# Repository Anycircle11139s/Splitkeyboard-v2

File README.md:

# SPLIT-KEYBOARD-V2
The second attempt of creating the prefect split keyboard by @NotALarp
## WHAT IS IT?
This is my custom split keyboard made in KiCad, based on a LILY58 split keyboard design, it is sleek and is designed with ergonomics in mind. 

## Featured Hardware:
- Nice!Nano v2 microcontroller
- Lipo batteries
- Low profile choc switches
- 0.91" OLED displays
- EC11 Rotary Encoders

## WHY I MADE IT
My first split keyboard was pretty bad, it was based on a xiao nrf58240 microcontroller, had a terrible layout and overall wasn't that good. So I decided that with my previous knowledge that I would create a new, second split keyboard. 

## NOTES AND DESIGN CHOICES
This  time I decided to base the layout on a real split keyboard and some better microcontrollers. I decided on the nice!nano v2 and based the layout on a Lily58 split keyboard which I think looks really good. I designed a custom, 3d-printed case which was created to be compact, modern and sleek. 

## GALLERY

<br>

## BOM
<br>
https://docs.google.com/document/d/1G1sLWLXkf7hAwwnX9o8N8jDjILno_Bk2AuGZwasASP0/edit?usp=sharing

<br>

<br>

|Name                           |Purpose                                         |Quantity|Total Cost (USD)|Link                                                                                                                                                                                                                                                                                                                                                                                                                                                                                                                                                                                                                                                                                                                                                                                 |Distributor    |
|-------------------------------|------------------------------------------------|--------|----------------|-------------------------------------------------------------------------------------------------------------------------------------------------------------------------------------------------------------------------------------------------------------------------------------------------------------------------------------------------------------------------------------------------------------------------------------------------------------------------------------------------------------------------------------------------------------------------------------------------------------------------------------------------------------------------------------------------------------------------------------------------------------------------------------|---------------|
|M3 screws                      |To screw everything into place                  |1       |3.00            |https://www.aliexpress.com/item/1005008810897680.html?algo_exp_id=087b4537-d427-4093-becf-17723da02467-6&pdp_ext_f=%7B%22order%22%3A%2211108%22%2C%22spu_best_type%22%3A%22price%22%2C%22eval%22%3A%221%22%2C%22fromPage%22%3A%22search%22%7D&utparam-url=scene%3Asearch%7Cquery_from%3A%7Cx_object_id%3A1005008810897680%7C_p_origin_prod%3A                                                                                                                                                                                                                                                                                                                                                                                                                                        |Ali express    |
|Keycaps                        |to cover the switches                           |1       |25.00           |https://www.aliexpress.com/item/1005006734545486.html?algo_exp_id=1f377480-5edc-41ad-8720-dc378dbb9e71-0&pdp_ext_f=%7B%22order%22%3A%221046%22%2C%22spu_best_type%22%3A%22price%22%2C%22eval%22%3A%221%22%2C%22fromPage%22%3A%22search%22%7D&utparam-url=scene%3Asearch%7Cquery_from%3A%7Cx_object_id%3A1005006734545486%7C_p_origin_prod%3A                                                                                                                                                                                                                                                                                                                                                                                                                                         |Ali express    |
|Case shipping and printing     |The 3D printed case                             |1       |0.00            |                                                                                                                                                                                                                                                                                                                                                                                                                                                                                                                                                                                                                                                                                                                                                                                     |Printing Legion|
|PCB                            |To hold/wire everything together                |1       |26.00           |                                                                                                                                                                                                                                                                                                                                                                                                                                                                                                                                                                                                                                                                                                                                                                                     |JLCPCB         |
|Rubber Feat                    |to keep the keyboard in place while typing      |1       |3.00            |https://www.aliexpress.com/item/1005009513504427.html?spm=a2g0o.productlist.main.2.402aMWEOMWEOzm&algo_pvid=8754c733-74ec-46fa-a026-dd8beb2eaa2f&algo_exp_id=8754c733-74ec-46fa-a026-dd8beb2eaa2f-1&pdp_ext_f=%7B%22order%22%3A%22398%22%2C%22spu_best_type%22%3A%22price%22%2C%22eval%22%3A%221%22%2C%22fromPage%22%3A%22search%22%7D&pdp_npi=6%40dis%21AUD%215.20%212.76%21%21%2124.88%2113.19%21%402101d6fe17791895784877032e32a2%2112000049332590820%21sea%21AU%217402515296%21X%211%210%21n_tag%3A-29919%3Bd%3A1851364a%3Bm03_new_user%3A-29895&curPageLogUid=5WTu2EJR6cb9&utparam-url=scene%3Asearch%7Cquery_from%3A%7Cx_object_id%3A1005009513504427%7C_p_origin_prod%3A                                                                                                      |Ali express    |
|Lipo batteries                 |For making the thing have power while wireless  |2       |14.00           |https://www.aliexpress.com/item/32660019420.html?spm=a2g0o.productlist.main.18.2d67kd2Qkd2Q7m&utparam-url=scene%3Asearch%7Cquery_from%3Apc_back_same_best%7Cx_object_id%3A32660019420%7C_p_origin_prod%3A&algo_pvid=c45310cf-be00-4c95-97ef-f2f4c851b03d&algo_exp_id=c45310cf-be00-4c95-97ef-f2f4c851b03d&pdp_ext_f=%7B%22order%22%3A%22188%22%2C%22fromPage%22%3A%22search%22%7D&pdp_npi=6%40dis%21AUD%216.66%213.99%21%21%214.69%212.81%21%402101e2b417791893788974036e0b69%2112000032763467394%21sea%21AU%217402515296%21X%211%210%21n_tag%3A-29919%3Bd%3A1851364a%3Bm03_new_user%3A-29895                                                                                                                                                                                        |Ali express    |
|JST pin connector              |To connect Lipo batteries                       |1       |1.30            |https://www.aliexpress.com/item/1005004955655144.html?spm=a2g0o.productlist.main.2.2a7463el63el05&algo_pvid=54c753d9-8154-4c75-a2fe-a480a0edb504&algo_exp_id=54c753d9-8154-4c75-a2fe-a480a0edb504-1&pdp_ext_f=%7B%22order%22%3A%224230%22%2C%22spu_best_type%22%3A%22price%22%2C%22eval%22%3A%221%22%2C%22fromPage%22%3A%22search%22%7D&pdp_npi=6%40dis%21AUD%211.38%211.31%21%21%210.97%210.92%21%40210311a017791891742303314e881a%2112000031146362162%21sea%21AU%217402515296%21X%211%210%21n_tag%3A-29919%3Bd%3A1851364a%3Bm03_new_user%3A-29895%3BpisId%3A5000000207008434&curPageLogUid=SeM6XgBLqABt&utparam-url=scene%3Asearch%7Cquery_from%3A%7Cx_object_id%3A1005004955655144%7C_p_origin_prod%3A                                                                            |Ali express    |
|Nice!Nano 2 drop in replacement|Microcontroller                                 |2       |12.00           |https://www.aliexpress.com/item/1005012324856273.html?spm=a2g0o.productlist.main.1.5312262dHECxbc&algo_pvid=1d39c1dc-7c31-4a60-900f-a0e3a6a7fce5&algo_exp_id=1d39c1dc-7c31-4a60-900f-a0e3a6a7fce5-0&pdp_ext_f=%7B%22order%22%3A%22-1%22%2C%22eval%22%3A%221%22%2C%22fromPage%22%3A%22search%22%7D&pdp_npi=6%40dis%21AUD%2113.71%212.19%21%21%2165.60%2110.50%21%402101f70717791880964281024e130c%2112000058098750531%21sea%21AU%217402515296%21X%211%210%21n_tag%3A-29919%3Bd%3A1851364a%3Bm03_new_user%3A-29895&curPageLogUid=t0nqsjWoAD10&utparam-url=scene%3Asearch%7Cquery_from%3A%7Cx_object_id%3A1005012324856273%7C_p_origin_prod%3A                                                                                                                                          |Ali express    |
|Rotary encoder                 |The turning sensor for volume/brightness control|2       |4.00            |https://www.aliexpress.com/item/1005006693443387.html                                                                                                                                                                                                                                                                                                                                                                                                                                                                                                                                                                                                                                                                                                                                |Ali express    |
|2M resistors                   |Battery sensing                                 |1       |2.30            |https://www.aliexpress.com/item/1005006984056678.html?spm=a2g0o.productlist.main.2.6d2bUmeuUmeuJY&algo_pvid=8428e61f-ef37-4c8f-9459-c9210825d6e1&algo_exp_id=8428e61f-ef37-4c8f-9459-c9210825d6e1-1&pdp_ext_f=%7B%22order%22%3A%22130%22%2C%22eval%22%3A%221%22%2C%22fromPage%22%3A%22search%22%7D&pdp_npi=6%40dis%21AUD%213.46%212.25%21%21%2116.54%2110.75%21%402103119c17791879033745560e8319%2112000038943042455%21sea%21AU%217402515296%21X%211%210%21n_tag%3A-29919%3Bd%3A1851364a%3Bm03_new_user%3A-29895&curPageLogUid=W9kpVUtpsgGF&utparam-url=scene%3Asearch%7Cquery_from%3A%7Cx_object_id%3A1005006984056678%7C_p_origin_prod%3A                                                                                                                                          |Ali express    |
|806K resistors                 |Battery Sense                                   |1       |2.30            |https://www.aliexpress.com/item/1005005184230104.html?spm=a2g0o.productlist.main.1.9292CUbcCUbcad&algo_pvid=8aa98164-e46b-4dea-8cd4-d1d9d648231d&algo_exp_id=8aa98164-e46b-4dea-8cd4-d1d9d648231d-0&pdp_ext_f=%7B%22order%22%3A%2217%22%2C%22eval%22%3A%221%22%2C%22fromPage%22%3A%22search%22%7D&pdp_npi=6%40dis%21AUD%212.39%212.27%21%21%2111.44%2110.87%21%402101eee917791877058268014e6261%2112000032017018125%21sea%21AU%217402515296%21X%211%210%21n_tag%3A-29919%3Bd%3A1851364a%3Bm03_new_user%3A-29895%3BpisId%3A5000000207008434&curPageLogUid=3ZB85ZmHR85W&utparam-url=scene%3Asearch%7Cquery_from%3A%7Cx_object_id%3A1005005184230104%7C_p_origin_prod%3A                                                                                                                |Ali express    |
|OLEDs                          |Displays                                        |2       |5.00            |https://www.aliexpress.com/item/1005009252203585.html                                                                                                                                                                                                                                                                                                                                                                                                                                                                                                                                                                                                                                                                                                                                |Ali express    |
|Diodes                         |For individual keys to click                    |1       |2.70            |https://www.aliexpress.com/item/1005007536719404.html?spm=a2g0o.productlist.main.1.48163d00gFi5nW&algo_pvid=8ca45988-0ebf-453f-8dbb-d071bb0fd947&algo_exp_id=8ca45988-0ebf-453f-8dbb-d071bb0fd947-0&pdp_ext_f=%7B%22order%22%3A%2257%22%2C%22spu_best_type%22%3A%22price%22%2C%22eval%22%3A%221%22%2C%22fromPage%22%3A%22search%22%7D&pdp_npi=6%40dis%21AUD%212.77%212.63%21%21%2113.25%2112.58%21%402101e2b617791874734143805e957b%2112000041199095476%21sea%21AU%217402515296%21X%211%210%21n_tag%3A-29919%3Bd%3A1851364a%3Bm03_new_user%3A-29895%3BpisId%3A5000000207008434&curPageLogUid=7tkJWryZP639&utparam-url=scene%3Asearch%7Cquery_from%3A%7Cx_object_id%3A1005007536719404%7C_p_origin_prod%3A                                                                            |Ali express    |
|Low Profile Choc Switches      |Buttons for the keyboard                        |1       |20.00           |https://www.aliexpress.com/item/1005005883472162.html?spm=a2g0o.productlist.main.4.4228tPMqtPMq2f&aem_p4p_detail=20260519032953288267209607090002622299&algo_pvid=d4c045f7-fedf-4b6d-a05c-4b18a162da60&algo_exp_id=d4c045f7-fedf-4b6d-a05c-4b18a162da60-3&pdp_ext_f=%7B%22order%22%3A%22820%22%2C%22eval%22%3A%221%22%2C%22fromPage%22%3A%22search%22%7D&pdp_npi=6%40dis%21AUD%2125.03%2121.54%21%21%2117.62%2115.16%21%40210318a717791865937722085eaeff%2112000034695877976%21sea%21AU%217402515296%21X%211%210%21n_tag%3A-29919%3Bd%3A1851364a%3Bm03_new_user%3A-29895%3BpisId%3A5000000207013346&curPageLogUid=ecY0FsHMIH2l&utparam-url=scene%3Asearch%7Cquery_from%3A%7Cx_object_id%3A1005005883472162%7C_p_origin_prod%3A&search_p4p_id=20260519032953288267209607090002622299_1|Ali Express    |

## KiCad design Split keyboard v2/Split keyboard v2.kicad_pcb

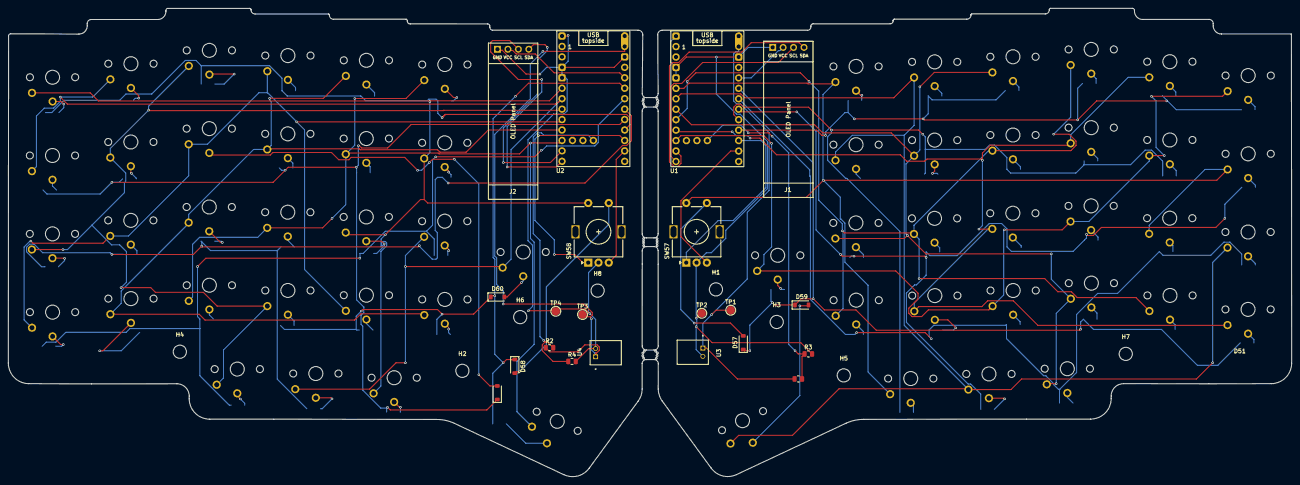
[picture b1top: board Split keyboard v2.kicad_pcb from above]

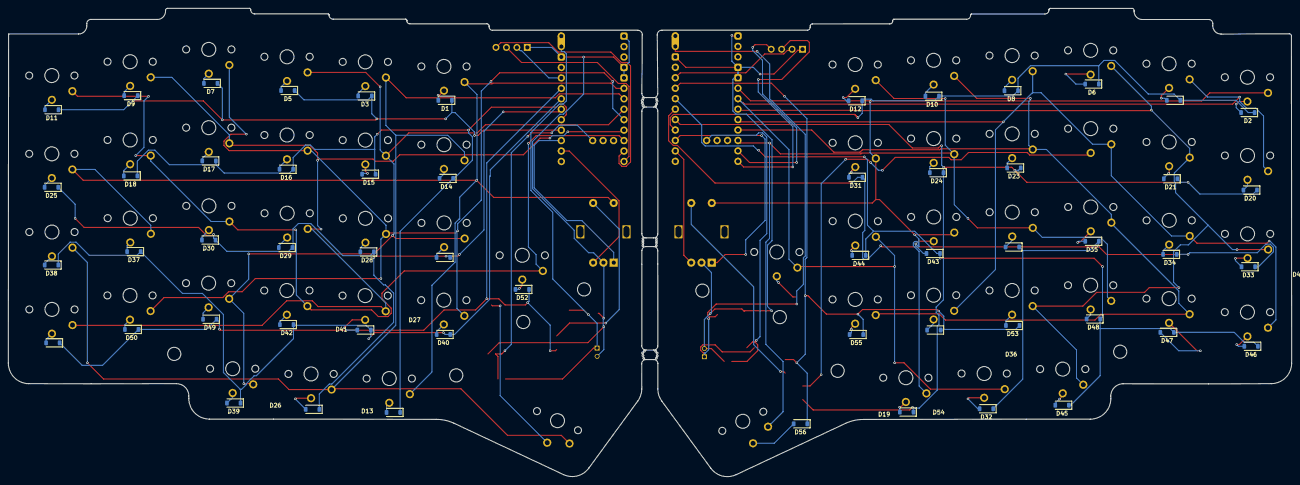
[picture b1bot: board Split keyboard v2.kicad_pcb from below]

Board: 2 copper layers, 312.1 x 113.9 mm, 142 parts (55 on the bottom side), 97 nets.

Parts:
CH1, CH2, CH3, CH4, CH5, CH6, CH7, CH8, CH9, CH10, CH11, CH12, CH13, CH14, CH15, CH16, CH17, CH18, CH19, CH20, CH21, CH22, CH23, CH24, CH25, CH26, CH27, CH28, CH29, CH30, CH31, CH32, CH33, CH34, CH35, CH36, CH37, CH38, CH39, CH40, CH41, CH42, CH43, CH44, CH45, CH46, CH47, CH48, CH49, CH50, CH51, CH52, CH53, CH54, CH55, CH56, CH57, CH58: choc_v1_SW_solder; SW_choc_v1_1u
D1, D2, D3, D4, D5, D6, D7, D8, D9, D10, D11, D12, D13, D14, D15, D16, D17, D18, D19, D20, D21, D22, D23, D24, D25, D26, D27, D28, D29, D30, D31, D32, D33, D34, D35, D36, D37, D38, D39, D40, D41, D42, D43, D44, D45, D46, D47, D48, D49, D50, D51, D52, D53, D54, D55, D56, D57, D58, D59, D60: D; D_SOD-123
H1, H2, H3, H4, H5, H6, H7, H8: MountingHole; MountingHole_3.2mm_M3
J1, J2: Conn_01x04_Socket; SSD1306-0.91-OLED-4pin-128x32
R1, R2: 806K; R_0805_2012Metric
R3, R4: 2M; R_0805_2012Metric
SW57, SW58: RotaryEncoder_Switch; RotaryEncoder_Alps_EC11E-Switch_Vertical_H20mm
TP1, TP3: BAT; TestPoint_Pad_D2.0mm
TP2, TP4: GND; TestPoint_Pad_D2.0mm
U1, U2: nice_nano; nice_nano_AH_USBup
U3, U4: S2B-PH-K-S(LF)(SN); JST_S2B-PH-K-S_LF__SN_

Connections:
/left/BT_PIN: R1.2, R3.1, U1.27 (P1.07-LF)
/left/COL0: CH1.1, CH13.1, CH25.1, CH37.1, SW57.S2, U1.5 (P0.17)
/left/COL1: CH3.1, CH15.1, CH27.1, CH39.1, CH57.1, U1.6 (P0.20)
/left/COL2: CH5.1, CH17.1, CH29.1, CH41.1, CH49.1, U1.7 (P0.22)
/left/COL3: CH7.1, CH19.1, CH31.1, CH43.1, CH51.1, U1.8 (P0.24)
/left/COL4: CH9.1, CH21.1, CH33.1, CH45.1, CH53.1, U1.9 (P1.00)
/left/COL5: CH11.1, CH23.1, CH35.1, CH47.1, CH55.1, U1.10 (P0.11)
/left/Encoder_A: SW57.A, U1.22 (P1.11-LF)
/left/Encoder_B: SW57.B, U1.23 (P0.10-LF)
/left/ROW0: D1.1 (K), D3.1 (K), D5.1 (K), D7.1 (K), D9.1 (K), D11.1 (K), U1.21 (P1.13-LF)
/left/ROW1: D13.1 (K), D14.1 (K), D15.1 (K), D16.1 (K), D17.1 (K), D18.1 (K), U1.20 (P1.15-LF)
/left/ROW2: D25.1 (K), D26.1 (K), D27.1 (K), D28.1 (K), D29.1 (K), D30.1 (K), U1.19 (P0.02-LF)
/left/ROW3: D37.1 (K), D38.1 (K), D39.1 (K), D40.1 (K), D41.1 (K), D42.1 (K), U1.18 (P0.29-LF)
/left/ROW4: D49.1 (K), D50.1 (K), D51.1 (K), D52.1 (K), D57.1 (K), D59.1 (K), U1.17 (P0.31-LF)
/left/SCL: J1.3, U1.12 (P1.06-LF)
/left/SDA: J1.4, U1.11 (P1.04-LF)
/left/VBAT: R1.1, TP1.1 (1_1), U1.13 (BAT+), U1.29 (BAT+), U3.1
/left/VCC: J1.2, U1.16 (3V3)
/right/BT_PIN: R2.2, R4.1, U2.27 (P1.07-LF)
/right/COL0: CH2.1, CH14.1, CH26.1, CH38.1, SW58.S2, U2.5 (P0.17)
/right/COL1: CH4.1, CH16.1, CH28.1, CH40.1, CH58.1, U2.6 (P0.20)
/right/COL2: CH6.1, CH18.1, CH30.1, CH42.1, CH50.1, U2.7 (P0.22)
/right/COL3: CH8.1, CH20.1, CH32.1, CH44.1, CH52.1, U2.8 (P0.24)
/right/COL4: CH10.1, CH22.1, CH34.1, CH46.1, CH54.1, U2.9 (P1.00)
/right/COL5: CH12.1, CH24.1, CH36.1, CH48.1, CH56.1, U2.10 (P0.11)
/right/Encoder_A: SW58.A, U2.22 (P1.11-LF)
/right/Encoder_B: SW58.B, U2.23 (P0.10-LF)
/right/ROW0: D2.1 (K), D4.1 (K), D6.1 (K), D8.1 (K), D10.1 (K), D12.1 (K), U2.21 (P1.13-LF)
/right/ROW1: D19.1 (K), D20.1 (K), D21.1 (K), D22.1 (K), D23.1 (K), D24.1 (K), U2.20 (P1.15-LF)
/right/ROW2: D31.1 (K), D32.1 (K), D33.1 (K), D34.1 (K), D35.1 (K), D36.1 (K), U2.19 (P0.02-LF)
/right/ROW3: D43.1 (K), D44.1 (K), D45.1 (K), D46.1 (K), D47.1 (K), D48.1 (K), U2.18 (P0.29-LF)
/right/ROW4: D53.1 (K), D54.1 (K), D55.1 (K), D56.1 (K), D58.1 (K), D60.1 (K), U2.17 (P0.31-LF)
/right/SCL: J2.3, U2.12 (P1.06-LF)
/right/SDA: J2.4, U2.11 (P1.04-LF)
/right/VBAT: R2.1, TP3.1 (1_1), U2.13 (BAT+), U2.29 (BAT+), U4.1
/right/VCC: J2.2, U2.16 (3V3)
GND: J1.1, J2.1, R3.2, R4.2, SW57.C, SW58.C, TP2.1 (1_1), TP4.1 (1_1), U1.3 (GND), U1.4 (GND), U1.14 (GND), U1.28 (GND), U2.3 (GND), U2.4 (GND), U2.14 (GND), U2.28 (GND), U3.2, U4.2
unnamed: CH1.2, D1.2 (A)
unnamed: CH2.2, D2.2 (A)
unnamed: CH3.2, D3.2 (A)
unnamed: CH4.2, D4.2 (A)
unnamed: CH5.2, D5.2 (A)
unnamed: CH6.2, D6.2 (A)
unnamed: CH7.2, D7.2 (A)
unnamed: CH8.2, D8.2 (A)
unnamed: CH9.2, D9.2 (A)
unnamed: CH10.2, D10.2 (A)
unnamed: CH11.2, D11.2 (A)
unnamed: CH12.2, D12.2 (A)
unnamed: CH13.2, D13.2 (A)
unnamed: CH15.2, D14.2 (A)
unnamed: CH17.2, D15.2 (A)
unnamed: CH19.2, D16.2 (A)
unnamed: CH21.2, D17.2 (A)
unnamed: CH23.2, D18.2 (A)
unnamed: CH14.2, D19.2 (A)
unnamed: CH16.2, D20.2 (A)
unnamed: CH18.2, D21.2 (A)
unnamed: CH20.2, D22.2 (A)
unnamed: CH22.2, D23.2 (A)
unnamed: CH24.2, D24.2 (A)
unnamed: CH25.2, D25.2 (A)
unnamed: CH27.2, D26.2 (A)
unnamed: CH29.2, D27.2 (A)
unnamed: CH31.2, D28.2 (A)
unnamed: CH33.2, D29.2 (A)
unnamed: CH35.2, D30.2 (A)
unnamed: CH26.2, D31.2 (A)
unnamed: CH28.2, D32.2 (A)
unnamed: CH30.2, D33.2 (A)
unnamed: CH32.2, D34.2 (A)
unnamed: CH34.2, D35.2 (A)
unnamed: CH36.2, D36.2 (A)
unnamed: CH37.2, D37.2 (A)
unnamed: CH39.2, D38.2 (A)
unnamed: CH41.2, D39.2 (A)
unnamed: CH43.2, D40.2 (A)
unnamed: CH45.2, D41.2 (A)
unnamed: CH47.2, D42.2 (A)
unnamed: CH38.2, D43.2 (A)
unnamed: CH40.2, D44.2 (A)
unnamed: CH42.2, D45.2 (A)
unnamed: CH44.2, D46.2 (A)
unnamed: CH46.2, D47.2 (A)
unnamed: CH48.2, D48.2 (A)
unnamed: CH49.2, D49.2 (A)
unnamed: CH51.2, D50.2 (A)
unnamed: CH53.2, D51.2 (A)
unnamed: CH55.2, D52.2 (A)
unnamed: CH50.2, D53.2 (A)
unnamed: CH52.2, D54.2 (A)
unnamed: CH54.2, D55.2 (A)
unnamed: CH56.2, D56.2 (A)
unnamed: D57.2 (A), SW57.S1
unnamed: D58.2 (A), SW58.S1
unnamed: CH57.2, D59.2 (A)
unnamed: CH58.2, D60.2 (A)

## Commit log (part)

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2026-06-11 Update README with CAD files link
    Added a link to Google Drive for CAD files.
2026-06-29 Add CAD folder to existing repo via LFS
